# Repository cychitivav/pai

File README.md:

<!--
MARKDOWN IMAGES & BADGES
* https://www.markdownguide.org/basic-syntax/#reference-style-links
* https://github.com/Ileriayo/markdown-badges

EMOJIS
* https://gist.github.com/rxaviers/7360908
  
Find and replace the following text with the name of the project:
	pai
-->

<div align="center" id="readme-top">

<!-- omit in toc -->
# PAI's project
Code and documentation for a UGV that can work and be teleoperated in a field.

[**Explore the docs »**](https://cychitivav.github.io/pai)

[View Demo](https://github.com/cychitivav/pai) · [Report Bug](https://github.com/cychitivav/pai/issues) · [Request Feature](https://github.com/cychitivav/pai/issues)

</div>

<!-- TABLE OF CONTENTS -->
<!-- omit in toc -->
## :pencil:Table of contents
- [:pushpin:About The Project](#pushpinabout-the-project)
	- [Built With](#built-with)
- [:checkered\_flag:Getting Started](#checkered_flaggetting-started)
	- [Prerequisites](#prerequisites)
	- [Installation](#installation)
	- [GitHub Codespace](#github-codespace)
- [:balloon:Usage](#balloonusage)
- [:key:License](#keylicense)
- [:pencil2:Authors](#pencil2authors)
- [:tada:Acknowledgments](#tadaacknowledgments)

<!-- ABOUT THE PROJECT -->
## :pushpin:About The Project

<div align="center">
	
</div>

Welcome to the PAI ROS 1 package repository! This package contains source code and documentation for a UGV that can work in a field. This project is part of the *PAI* subject at the Universidad Nacional de Colombia.

> __Note__: This package is being developed using ROS noetic 

<!-- BADGES
https://github.com/Ileriayo/markdown-badges -->
### Built With
* 
* 
* 

<!-- GETTING STARTED -->
## :checkered_flag:Getting Started

This is an example of how you may give instructions on setting up your project locally.
	To get a local copy up and running follow these simple example steps.

### Prerequisites
In order to avoid installing ROS on your local machine, we will be using a docker image to run ROS. So, you will just need to install [Docker](https://docs.docker.com/get-docker/) in your local machine.

### Installation

1. Clone the repo
	```bash
	git clone https://github.com/cychitivav/pai.git
	```
2. Build the docker image
	```bash
	docker build -t pai:latest .
	```
3. Run the docker image
	```bash
	docker run -it \
     		   --rm \
			   -v /tmp/.X11-unix:/tmp/.X11-unix:rw \
               -v $PWD:/root/catkin_ws/src/pai \
			   --name pai \
			   pai:latest
	```
	> __Note__: If you have troubles with the display, try to run the following command before running the docker image:
	> ```bash
	> xhost +local:root
	> ```

### GitHub Codespace
Codespaces add an easy way to start contributing to this project. Some extra step are needed to run the visualization in a remote machine. You need to create a GitHub Codespace:

1. To create a Codespace, click on the following button:

2. Choose the configuration that best suits you (A high performance configuration is recommended)
3. Wait for the Codespace to be created and set up (It will appear a terminal which is running some scripts)
4. Set a password for the root user
	```bash	
	passwd
	```

From your local machine, you will need to run the following command:

```bash	
gh cs ssh -- -XY
```

> __Note__: You need to have the [GitHub CLI](https://cli.github.com/manual/installation) installed in your local machine.

Then, select the Codespace that you want to connect to and enter the password that you set before.

<!-- USAGE EXAMPLES -->
## :balloon:Usage
In order to run the package, you will need to follow the next steps from the workspace directory (by default, `~\catkin_ws`):

1. Compile packages
```bash
catkin build
```
1. Source the workspace
```bash
source devel/setup.bash
```
1. Launch the package
```bash
roslaunch pai view_robot.launch
```

<!-- ROADMAP -->
<!-- ## :roller_coaster:Roadmap

- [ ] Feature 1
- [ ] Feature 2
    - [ ] Nested Feature

> __Note__: See the [open issues](https://github.com/cychitivav/pai/issues) for a full list of proposed features (and known issues). -->

<!-- CONTRIBUTING -->
<!-- ## :busts_in_silhouette:Contributing

If you have a suggestion that would make this better, please create a pull request.

1. Create your Branch (`git checkout -b <type>/<name>`)
2. Commit your Changes (`git commit -m 'Add some AmazingFeature'`)
3. Push to the Branch (`git push origin <type>/<name>`)
4. Open a Pull Request (in the `git push` response, it appears a link to open a PR) 

The available contribution types are:
* `docs`
* `feat`
* `dev`
* `fix`

Don't forget to give the project a star! Thanks again!
 -->

<!-- LICENSE -->
## :key:License
Distributed under the MIT License. See [`LICENSE`](LICENSE) for more information.

<!-- CONTACT -->
## :pencil2:Authors
* [@cychitivav](https://github.com/cychitivav)
* [@jsduenass](https://github.com/jsduenass)
* [@juvallejom](https://github.com/juvallejom)
* [@Canborda](https://github.com/canborda)
* [@Camilo96A](https://github.com/camilo96a)
* [@jodiazro](https://github.com/jodiazro)

<!-- ACKNOWLEDGMENTS -->
## :tada:Acknowledgments

* Thanks to the [SIMA student group]() who help out supporting this project.

<div align="right">

[:arrow_double_up:back to top](#readme-top)
</div>

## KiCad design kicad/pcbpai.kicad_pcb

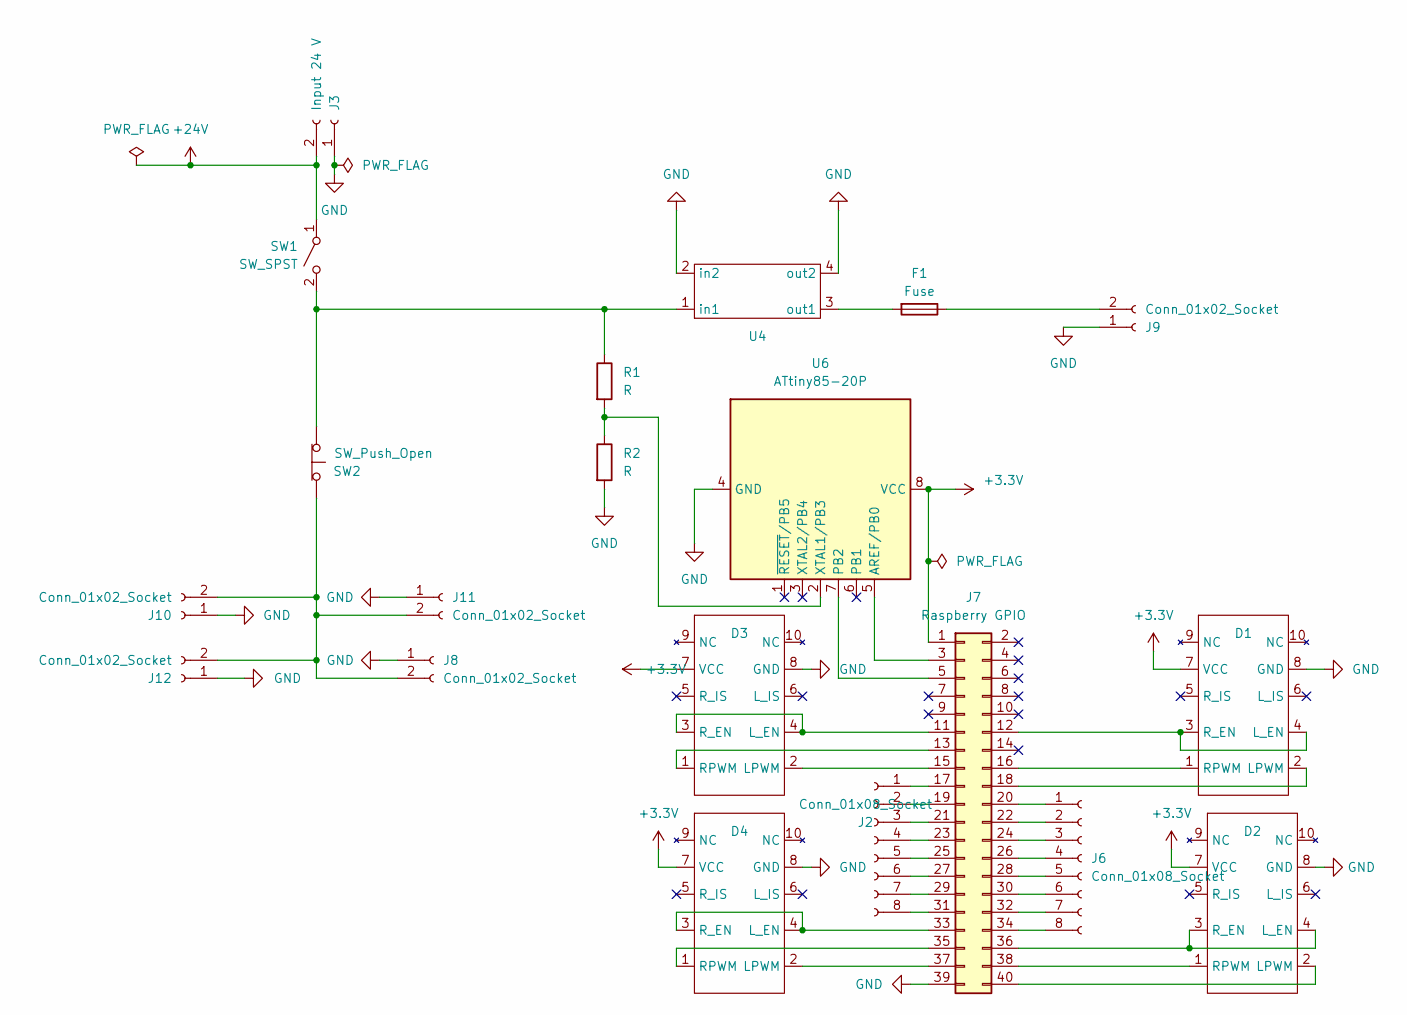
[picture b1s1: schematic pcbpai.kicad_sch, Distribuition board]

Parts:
D1, D2, D3, D4: IDC-Header_2x05_P2.54mm_Vertical
F1: Fuse; fuse
J2, J6: Conn_01x08_Socket; PinSocket_1x08_P2.54mm_Vertical
J3: Input 24 V; AMASS_XT60-M_1x02_P7.20mm_Vertical
J7: Raspberry GPIO; IDC-Header_2x20_P2.54mm_Vertical
J8, J10, J11, J12: Conn_01x02_Socket; PhoenixContact_MSTBA_2,5_2-G_1x02_P5.00mm_Horizontal
J9: Conn_01x02_Socket; TerminalBlock_Phoenix_PT-1,5-2-5.0-H_1x02_P5.00mm_Horizontal
R1, R2: R; R_Axial_DIN0207_L6.3mm_D2.5mm_P7.62mm_Horizontal
SW1: SW_SPST; PhoenixContact_MSTBA_2,5_2-G_1x02_P5.00mm_Horizontal
SW2: SW_Push_Open; PhoenixContact_MSTBA_2,5_2-G_1x02_P5.00mm_Horizontal
U4: regulator
U6: ATtiny85-20P; DIP-8_W7.62mm

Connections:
+3.3V: D1.7 (VCC), D2.7 (VCC), D3.7 (VCC), D4.7 (VCC), J7.1, U6.8 (VCC)
+24V: J3.2, SW1.1 (A)
GND: D1.8 (GND), D2.8 (GND), D3.8 (GND), D4.8 (GND), J3.1, J7.39, J8.1, J9.1, J10.1, J11.1, J12.1, R2.2, U4.2 (in2), U4.4 (out2), U6.4 (GND)
unnamed: D1.2 (LPWM), J7.18
unnamed: D1.3 (R_EN), D1.4 (L_EN), J7.12
unnamed: D1.1 (RPWM), J7.16
unnamed: D2.2 (LPWM), J7.40
unnamed: D2.3 (R_EN), D2.4 (L_EN), J7.36
unnamed: D2.1 (RPWM), J7.38
unnamed: D3.2 (LPWM), J7.15
unnamed: D3.3 (R_EN), D3.4 (L_EN), J7.11
unnamed: D3.1 (RPWM), J7.13
unnamed: D4.2 (LPWM), J7.37
unnamed: D4.3 (R_EN), D4.4 (L_EN), J7.33
unnamed: D4.1 (RPWM), J7.35
unnamed: J2.1, J7.17
unnamed: J2.2, J7.19
unnamed: J2.3, J7.21
unnamed: J2.4, J7.23
unnamed: J2.5, J7.25
unnamed: J2.6, J7.27
unnamed: J2.7, J7.29
unnamed: J2.8, J7.31
unnamed: J6.1, J7.20
unnamed: J6.2, J7.22
unnamed: J6.3, J7.24
unnamed: J6.4, J7.26
unnamed: J6.5, J7.28
unnamed: J6.6, J7.30
unnamed: J6.7, J7.32
unnamed: J6.8, J7.34
unnamed: J7.3, U6.5 (AREF/PB0)
unnamed: J7.5, U6.7 (PB2)
unnamed: F1.1, J9.2
unnamed: J8.2, J10.2, J11.2, J12.2, SW2.2 (B)
unnamed: R1.1, SW1.2 (B), SW2.1 (A), U4.1 (in1)
unnamed: F1.2, U4.3 (out1)
unnamed: R1.2, R2.1, U6.2 (XTAL1/PB3)

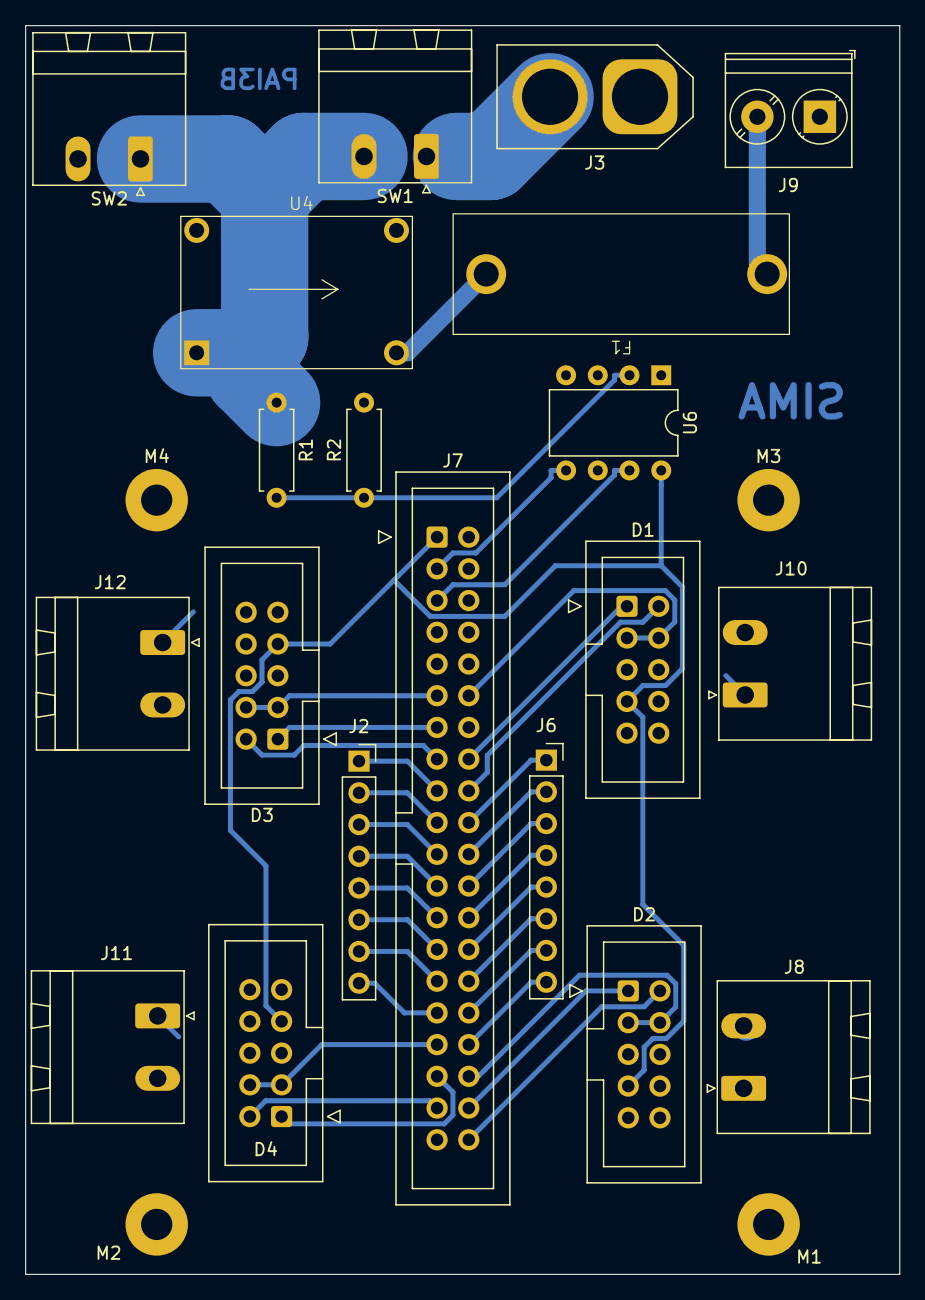
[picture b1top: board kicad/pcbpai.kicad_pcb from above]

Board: 2 copper layers, 70.0 x 100.0 mm, 24 parts (0 on the bottom side), 38 nets.

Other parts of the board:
M1, M2, M3, M4: MountingHole_2.5mm_Pad

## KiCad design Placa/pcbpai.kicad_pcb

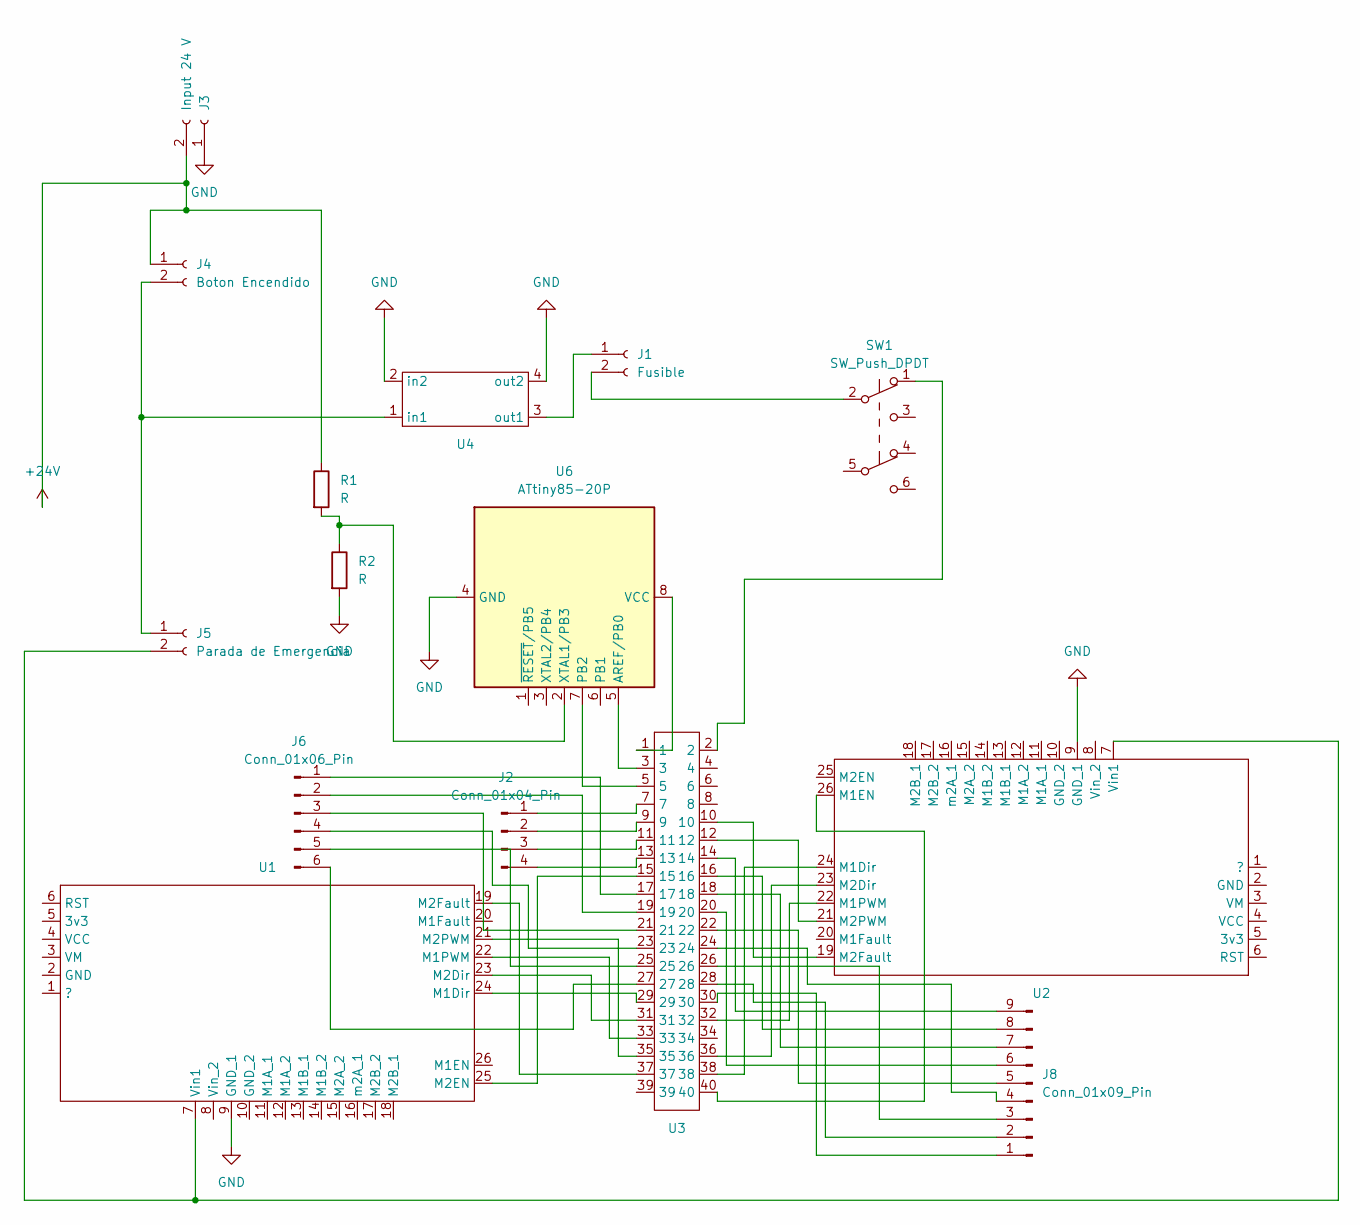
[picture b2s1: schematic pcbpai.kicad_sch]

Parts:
J1: Fusible; fusible
J2: Conn_01x04_Pin; PinHeader_1x04_P2.54mm_Vertical
J3: Input 24 V; Altech_AK300_1x02_P5.00mm_45-Degree
J4: Boton Encendido; Altech_AK300_1x02_P5.00mm_45-Degree
J5: Parada de Emergencia; Altech_AK300_1x02_P5.00mm_45-Degree
J6: Conn_01x06_Pin; PinSocket_1x06_P2.54mm_Vertical
J8: Conn_01x09_Pin; PinHeader_1x09_P2.54mm_Vertical
R1, R2: R; R_Axial_DIN0207_L6.3mm_D2.5mm_P7.62mm_Horizontal
SW1: SW_Push_DPDT; pulsador
U1, U2: Pololu MAX 14870 Dual Shield Arduino
U3: raspberry
U4: regulador
U6: ATtiny85-20P; DIP-8_W7.62mm

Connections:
+24V: J3.2, J4.1, R1.1
GND: J3.1, R2.2, U1.9 (GND_1), U2.9 (GND_1), U4.2 (in2), U4.4 (out2), U6.4 (GND)
unnamed: J1.1, U4.3 (out1)
unnamed: J1.2, SW1.2 (B)
unnamed: J2.1, U3.7
unnamed: J2.2, U3.9
unnamed: J2.3, U3.11
unnamed: J2.4, U3.13
unnamed: J4.2, J5.1, U4.1 (in1)
unnamed: J5.2, U1.7 (Vin1), U2.7 (Vin1)
unnamed: J6.1, U3.17
unnamed: J6.2, U3.19
unnamed: J6.3, U3.21
unnamed: J6.4, U3.23
unnamed: J6.5, U3.25
unnamed: J6.6, U3.27
unnamed: J8.1, U3.30
unnamed: J8.2, U3.28
unnamed: J8.3, U3.26
unnamed: J8.4, U3.24
unnamed: J8.5, U3.22
unnamed: J8.6, U3.20
unnamed: J8.7, U3.18
unnamed: J8.8, U3.16
unnamed: J8.9, U3.14
unnamed: SW1.1 (A), U3.2
unnamed: U1.24 (M1Dir), U3.29
unnamed: U1.22 (M1PWM), U3.33
unnamed: U1.23 (M2Dir), U3.31
unnamed: U1.25 (M2EN), U3.15
unnamed: U1.19 (M2Fault), U3.37
unnamed: U1.21 (M2PWM), U3.35
unnamed: U2.24 (M1Dir), U3.38
unnamed: U2.26 (M1EN), U3.40
unnamed: U2.22 (M1PWM), U3.32
unnamed: U2.23 (M2Dir), U3.36
unnamed: U2.19 (M2Fault), U3.10
unnamed: U2.21 (M2PWM), U3.12
unnamed: U3.3, U6.5 (AREF/PB0)
unnamed: U3.5, U6.7 (PB2)
unnamed: U3.1, U6.8 (VCC)
unnamed: R1.2, R2.1, U6.2 (XTAL1/PB3)

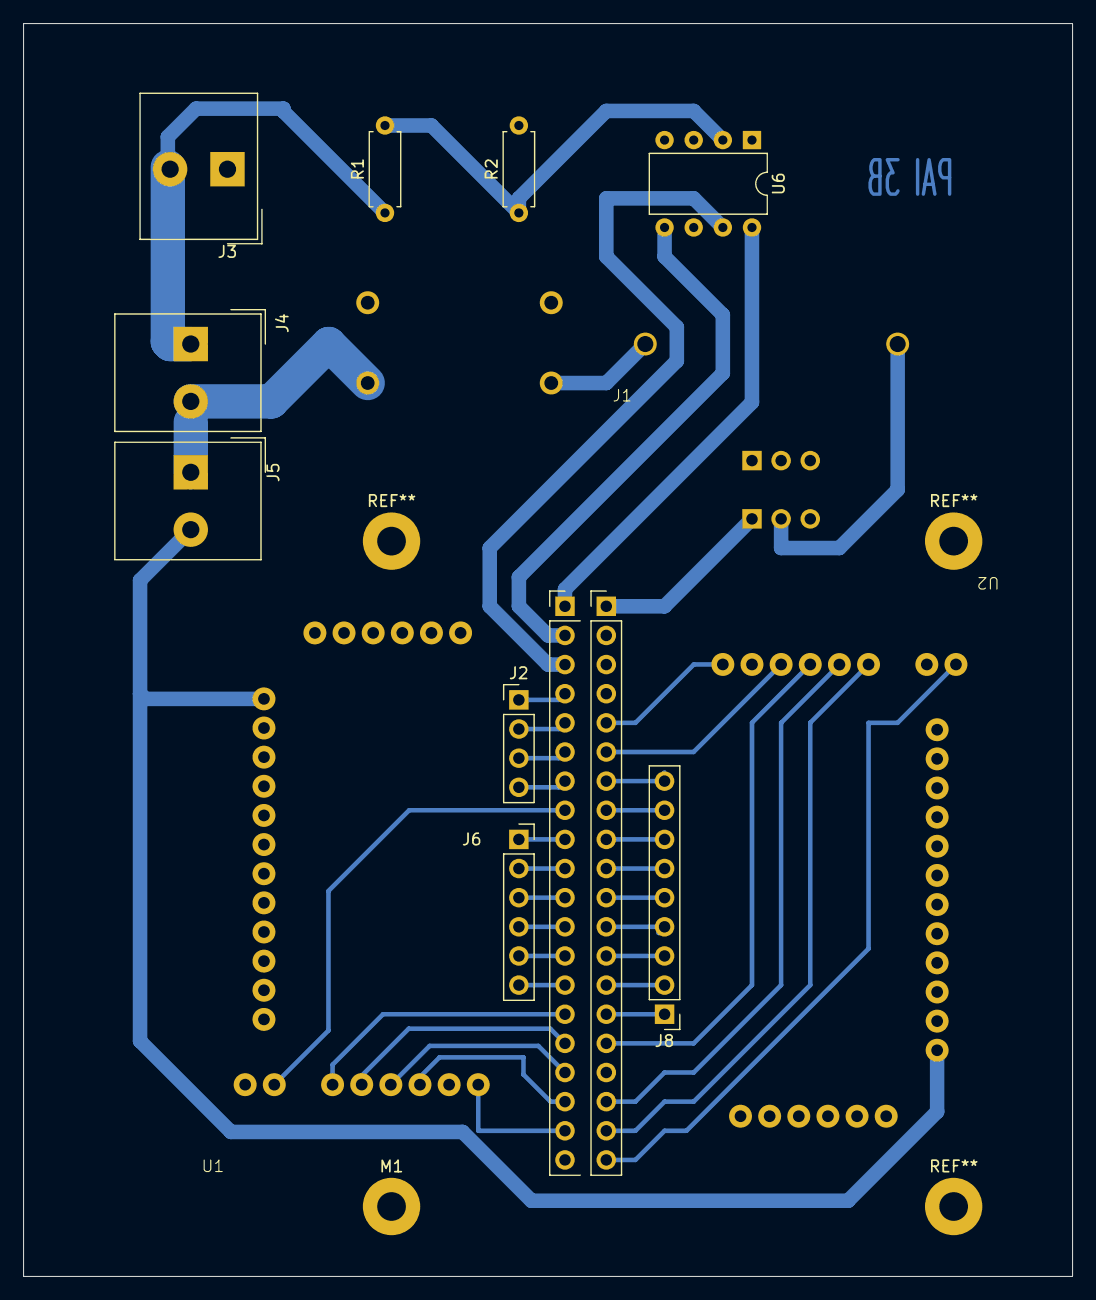
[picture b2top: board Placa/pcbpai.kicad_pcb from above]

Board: 2 copper layers, 91.4 x 109.2 mm, 16 parts (0 on the bottom side), 42 nets.

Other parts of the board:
M1: MountingHole_2.5mm_Pad

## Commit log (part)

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2023-05-01 add first docker conf
2023-05-01 add dependencies to build pdf docs
2023-05-01 add first documentation
2023-05-01 change theme to book and add first html
2023-05-01 add book sphinx theme to dependencies
2023-05-01 add github action to publish docs
2023-05-01 add requirements file to dockerfile
2023-05-02 add kinematics damping system calculations implementation of the inverse kinematics of the damping system to find the position of the linkages and calculate the force of produce by the damper station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
2023-05-02 fix make documentation
2023-05-02 remove build documentation
2023-05-02 add doc8 verification - doc8 verification - fix action - fix README links
2023-05-02 remove sphinx dependencies from Dockerfile
2023-05-02 build documentation action (#11)
    * add doc8 verification
    - doc8 verification
    - fix action
    - fix README links
    * fix build documentation action
    * update README
2023-05-02 test ls actions
2023-05-02 test without pip options
2023-05-02 add branch to push trigger
2023-05-02 fix docs path bugs
2023-05-02 deploy: 8f8a16e4b8d0ef8c556dcda8cb29a4e1234b4cfc
2023-05-02 Revert "build documentation action (#11)"
    This reverts commit f5a3299c4bcd14920e9226d0a3f50cc0365f5d1d.
2023-05-02 fix gh-pages branch in actions
2023-05-02 deploy: c7314286d379e1133e1831a153d92d34b7664ed0
2023-05-02 remove dev branch from gh-pages action
2023-05-02 update setup python job
2023-05-02 fix python version
2023-05-03 add test docs script
2023-05-03 edit README to fix badges
2023-05-03 split action inn two jobs
2023-05-03 fix path not found bug and add on docs branch activation
2023-05-03 fix \ bug
2023-05-03 change artifact directory
2023-05-03 change artifact directory to ~
2023-05-03 test without setup python
2023-05-03 add upload to gh-pages job
2023-05-03 change upload page to gh-pages
2023-05-03 deploy: 93b35f7192eafb0a4036bb53088381951a6bd70b
2023-05-03 add deploy in action
2023-05-03 fix permissions
2023-05-03 remove test_docs shell due to docs branches added to action
2023-05-03 remove test_docs shell due to docs branches added to action (#16)
2023-05-03 test action from docs/* branch
2023-05-03 deploy: 13f531f19db96b6c9e08254c08e786d059c21191
2023-05-03 deploy: 33c3f169c07a3221325a80dc5635c868c865ec52
2023-05-03 add content for the README file (#18)
2023-05-03 add make pdf
2023-05-03 add latex dependencies
2023-05-03 fix bug make doctests
2023-05-04 add damper kinetics and force analysis
2023-05-04 add kinematics calculations wheel system
2023-05-04 refactor name convention from spanish to english
2023-05-04 add make pdf to download it as a artifact (#19)
    * add make pdf
    * add latex dependencies
    * fix bug make doctests
2023-05-04 split make pdf and html in two actions
    deactivate on push trigger
    remove gh-pages upload
2023-05-04 fix job name
2023-05-04 fix job name (#22)
    * add make pdf
    * add latex dependencies
    * fix bug make doctests
    * split make pdf and html in two actions
    deactivate on push trigger
    remove gh-pages upload
2023-05-06 change test order
2023-05-06 add forward kinematics python
2023-05-14 add animation
2023-05-16 motor calculations simplified
2023-05-16 deploy: 7483f5241ed6668dcdd6604f5491a0927539a475
2023-05-16 add max obstacle added
2023-05-16 improve plots
2023-05-16 add jupyter dependencies
2023-05-16 remove myst parser due to myst-nb
2023-05-16 fix titles no consecutive
2023-05-16 fix toctree
2023-05-16 set off execution nb
2023-05-16 add content to wheel notebook
2023-05-16 deploy: bad583ebf03f4e84a2e794aff36bf50f16740456
2023-05-16 add exexcution
2023-05-16 deploy: 8c244f259e38420f83b2cc469ce61d76dcbb5650
2023-05-24 Added ros package & robot urdf description
2023-05-24 Added meshes & measures for urdf description
2023-05-24 deploy: f2fc0f029cb03fc948b0d1e6543fd84f0a0ce7c9
2023-05-24 add wheel mesh
2023-05-24 modify urdf
2023-05-24 add center mesh
2023-05-24 update docker image to ros noetic
2023-05-24 fix Dockerfile
2023-05-29 add kinematic model
2023-05-30 docs: update ROS version in documentantion - Reflect change from ROS 2 to ROS 1 in the documentation - Specify ROS noetic is being use in the development of the package - Set license parameter in ROS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
2023-05-31 Dev/ros package (#24)
    * Added ros package & robot urdf description
    * add wheel mesh
    * modify urdf
    * add center mesh
    * Added meshes & measures for urdf description
    * update docker image to ros noetic
2023-06-02 [FEAT]: add driver library
2023-06-03 modify urdf with xacro macro
2023-06-03 add simulation launch
2023-06-03 break experomental
2023-06-03 add rqt dependencies
2023-06-03 remove submodule
2023-06-03 add setup
2023-06-04 fix left wheels
2023-06-04 add hardware interface
2023-06-04 remove view_robot.urdf after merge
2023-06-04 fix wording
2023-06-04 change docker base image
2023-06-04 add max velocity parameter
    - define a linear and angular velocity limit
2023-06-05 add comments with reference of the math used
2023-06-05 Dev/kinematic model (#25)
    * modify urdf with xacro macro
    * add simulation launch
    * add rqt dependencies
    * fix left wheels
    * add hardware interface
    * remove view_robot.urdf after merge
2023-06-05 add attiny reader
2023-06-05 [FEAT]: driver node - create driver node subscriber - document raspberry set up process
2023-06-05 [REFACT]: motor_driver subs - split call_back for indivual motor velocity message - doc testing pub messages
2023-06-05 finish arduino program for attiny85
2023-06-05 add battery node
2023-06-05 add battery script to cmakelists
2023-06-05 fix import std_msgs
2023-06-05 custom service
2023-06-05 fix srv data
2023-06-05 fix battery constants
2023-06-05 fix power battery names
2023-06-05 refactor attiny name
2023-06-05 fix BatteryState msg
2023-06-05 [FEAT]: driver pin out param - driver pinout configured through ros param
2023-06-05 [FEAT]: driver pin out param - driver pinout configured through ros param - manage exceptions of pinout param not being found
2023-06-05 add rospy logs
2023-06-06 change pin to PB3 in arduino file
2023-06-06 change voltage to float 32 in srv
2023-06-06 add documetation for bootloader attiny85
2023-06-06 Dockerfile remove sourcing ROS
2023-06-06 streamline getting rosparameters
2023-06-06 change image
2023-06-06 [DOCS]: separate raspberry pin documentation - split electronics documentation into its own page - remove local image
2023-06-06 [FEAT]: remove max14870 lib from source code - remove the lib and add it as a submodule
2023-06-06 [FIX]: remove duplicate pionut documentation - remove pionut from index file in documentation as is duplicated - remove redundant drivers_pinout
2023-06-06 add service response
2023-06-06 [FIX]: launch file param
2023-06-06 Dev/motor drivers (#26)
    * [FEAT]: add driver library
    * docs: raspberry pin out
    * break experomental
    * remove submodule
    * [FEAT]: add library
    * add setup
2023-06-06 add `apt update` to build_pdf action
2023-06-06 remove lib from motor_driver.py
2023-06-06 remove lib instance and add pigpiod remote
2023-06-06 remove lib submodule
2023-06-06 remove gitmodule
2023-06-06 remove inheritance from battery node
2023-06-07 install `pigpiod` from apt
2023-06-07 [FEAT] add devcontainer config
2023-06-07 [FEAT]: driver with no arguments
    - configure driver to run with no arguments.
2023-06-07 Fix/driver lib remote (#29)
    * remove lib from motor_driver.py
    * remove lib instance and add pigpiod remote
    * add pigpiod to Dockerfile for use outside raspi
    * remove lib submodule
    * remove gitmodule
    * install `pigpiod` from pip
2023-06-08 [FIX]: change default pin out
2023-06-08 change four topics to two topics
2023-06-08 change PWM to software
2023-06-09 update pins to handle PWM through software and hardware
2023-06-09 fix joint names in controller parameters
    Close #30
2023-06-09 add ros control dependencies to Dockerfile
2023-06-10 [FIX]: joint names in controller parameters (#32)
2023-06-10 remove backup and cache files
2023-06-10 add backup folders to gitignore
2023-06-10 add footprints
2023-06-11 add latexpdf style
2023-06-11 update fonts in action
2023-06-11 change index to rst
2023-06-11 order docs folders and rename action files
2023-06-11 change latex document type to article
2023-06-11 add trigger to build pdf
2023-06-11 add trigger sphinx_html.yml
2023-06-11 fix index.rst
2023-06-11 remove pip dependencies from test action
2023-06-12 remove test from actions
2023-06-12 move fonts folder
2023-06-12 add files with titles and initial content
    ---------
2023-06-12 remove test doc8 from Makefile
2023-06-12 add favicon
2023-06-12 fix broken links
2023-06-12 add list of figures and tables
2023-06-13 add final documentation ---------
2023-06-13 speed slow change
2023-06-13 change frequency to 160Hz
2023-06-13 add signal shutdown detection
2023-06-13 add on shutdown callback
2023-06-14 [FEAT]: separate ramp into independent function - create change of direction protection feature - remove ramp behavior from set_speed into a independent function
2023-06-14 [FEAT]: ramp and pwm change direction protection (#39)
    * speed slow change
    * fix negative change
    * change frequency to 160Hz
    * add signal shutdown detection
    * add on shutdown callback
    * [FEAT]: separate ramp into independent function
2023-06-14 Revert "[FEAT]: ramp and pwm change direction protection (#39)" (#41)
    This reverts commit 48275a6a935ebef47f731a84f05b0457bfe6c0cc.
2023-06-14 move fault callback to fault code section
2023-06-14 refactor set_speed function in driver class
2023-06-15 refactor kicad folder
2023-06-15 add 3d models and footprints to kicad
2023-06-15 [DOCS]: fix slow boot time
2023-06-15 center raspberry mounting holes
2023-06-16 add fuse 3d model
2023-06-17 add termninal blocks for sensors and 24+ zone
2023-06-18 comment single motor arduino
2023-06-18 [FEAT]: single motor testing new BTS7960 drivers
2023-06-19 add autostart pigpio deamon docs
2023-06-20 add control from an arduino mega and BTS7960 library
    ---------
2023-06-20 modify pins new drivers (BTS7960)
2023-06-20 change logic for BTS7960 driver
2023-06-20 add remap for 4 drivers
2023-06-20 fix regulator model
2023-06-20 finish pcb
2023-06-20 add gerber files and change footprints
2023-06-21 fix xt60 polarity
2023-06-21 edit footprints
2023-06-21 add f.cu layer in gerbers
2023-06-21 unfix xt60 polarity
2023-06-24 testing motor driver BTS7960 (#45)
    * [FEAT]: single motor testing new BTS7960 drivers
    * [FEAT]: adding multiple motors
    * comment single motor arduino
    * add control from an arduino mega and BTS7960 library
    ---------
    * modify pins new drivers (BTS7960)
2023-06-24 Docs/software setup (#46)
    * [DOCS]: fix slow boot time
    * add autostart pigpio deamon docs
    ---------
2023-06-24 change switch and fuse symbols
2023-06-24 Dev/pcb (#44)
    * remove backup and cache files
    * remove extra README files
    * add backup folders to gitignore
    * add footprints
    * refactor kicad folder
    * add 3d models and footprints to kicad
2023-06-30 remove MAX DUAL14870 license
2023-07-05 Fix path in pigpiod setup
2023-07-05 Update driver pins
2023-07-05 Add i2c setup to docs
2023-07-05 fix sys argv length
2023-07-05 fix battery detect i2c attiny
2023-07-05 Replace sys.argv with rospy.myargv
2023-07-07 Add utils
2023-07-07 Add software setup and electronics to toctree docs
2023-07-12 Add badges for kicad and raspberry
2023-07-12 add authors
2023-07-12 Clean devcontainer
2023-07-12 Add workspace folder
2023-07-12 Fix workspace folder
2023-07-13 Add ssh to devcontainer
2023-07-13 Remove env from dockerfile
2023-07-13 Fix simulation and comment velocity limits in kinematic model (#49)
2023-07-13 Fix tipo '_wheel' and add xauth to devcontainer
2023-07-13 Add git to devcontainer
2023-07-13 Fix/dev container display (#52)
    * Fix simulation and comment velocity limits in kinematic model
    * Clean devcontainer
    * Add workspace folder
    * Fix workspace folder
    * Change workspace mount and source catkin build
    * Add ssh to devcontainer
2023-07-13 Document Codespace configuration in README
